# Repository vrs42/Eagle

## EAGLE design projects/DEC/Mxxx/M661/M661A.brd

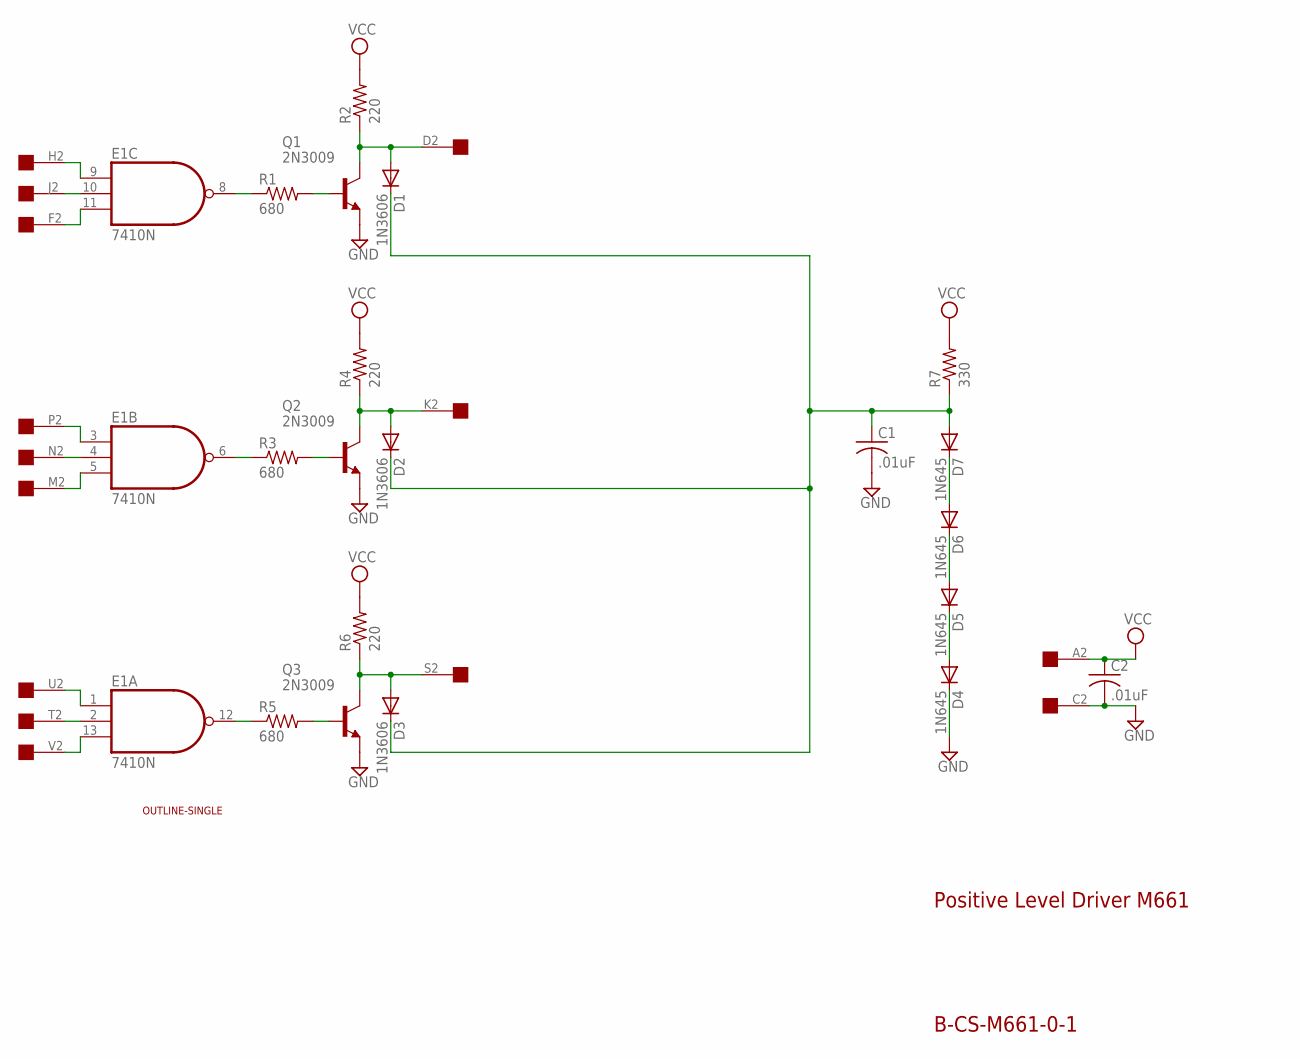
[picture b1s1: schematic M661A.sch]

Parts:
C1, C2: .01uF; C050-025X075
D1, D2, D3: 1N3606; DO35-10
D4, D5, D6, D7: 1N645; DO35-10
E1: 7410N; DIL14
Q1, Q2, Q3: 2N3009; TO5
R1, R3, R5: 680; 0207/10
R2, R4, R6: 220; 0207/10
R7: 330; 0207/10
U$1: OUTLINE-SINGLE; SINGLE
U$3: EDGE-1; EDGE-CON1

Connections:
GND: C1.2, C2.2, D4.C, E1.7 (GND), Q1.1 (E), Q2.1 (E), Q3.1 (E), U$3.C2
unnamed: E1.10 (I1), U$3.J2
unnamed: E1.9 (I0), U$3.H2
unnamed: E1.8 (O), R1.1
unnamed: Q1.2 (B), R1.2
unnamed: E1.4 (I1), U$3.N2
unnamed: D1.A, Q1.3 (C), R2.1, U$3.D2
unnamed: E1.2 (I1), U$3.T2
unnamed: E1.1 (I0), U$3.U2
unnamed: E1.3 (I0), U$3.P2
unnamed: E1.6 (O), R3.1
unnamed: D2.A, Q2.3 (C), R4.1, U$3.K2
unnamed: C1.1, D1.C, D2.C, D3.C, D7.A, R7.1
unnamed: D4.A, D5.C
unnamed: D5.A, D6.C
unnamed: E1.5 (I2), U$3.M2
unnamed: Q2.2 (B), R3.2
unnamed: E1.12 (O), R5.1
unnamed: D3.A, Q3.3 (C), R6.1, U$3.S2
unnamed: D6.A, D7.C
unnamed: E1.11 (I2), U$3.F2
unnamed: E1.13 (I2), U$3.V2
unnamed: Q3.2 (B), R5.2
VCC: C2.1, E1.14 (VCC), R2.2, R4.2, R6.2, R7.2, U$3.A2

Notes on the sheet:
Positive Level Driver M661
B-CS-M661-0-1

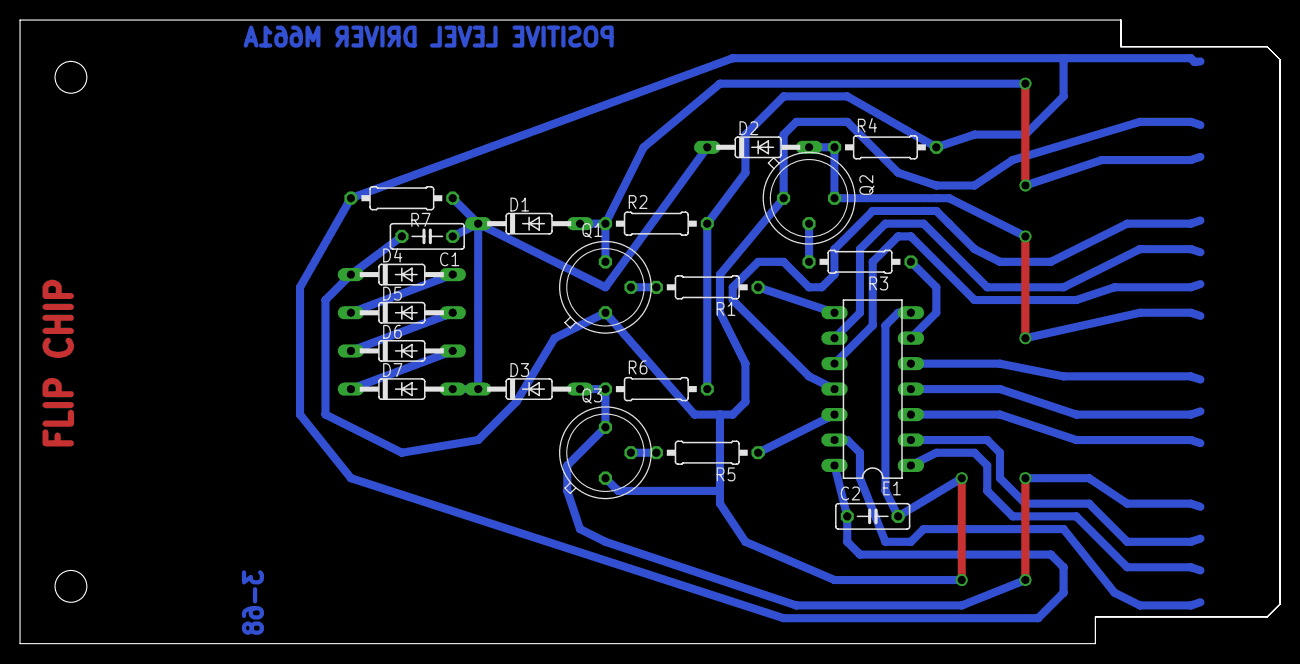
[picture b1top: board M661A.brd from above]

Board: 2 copper layers, 125.7 x 62.2 mm, 23 parts (0 on the bottom side), 24 nets.

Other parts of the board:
U$2: FLIPCHIP

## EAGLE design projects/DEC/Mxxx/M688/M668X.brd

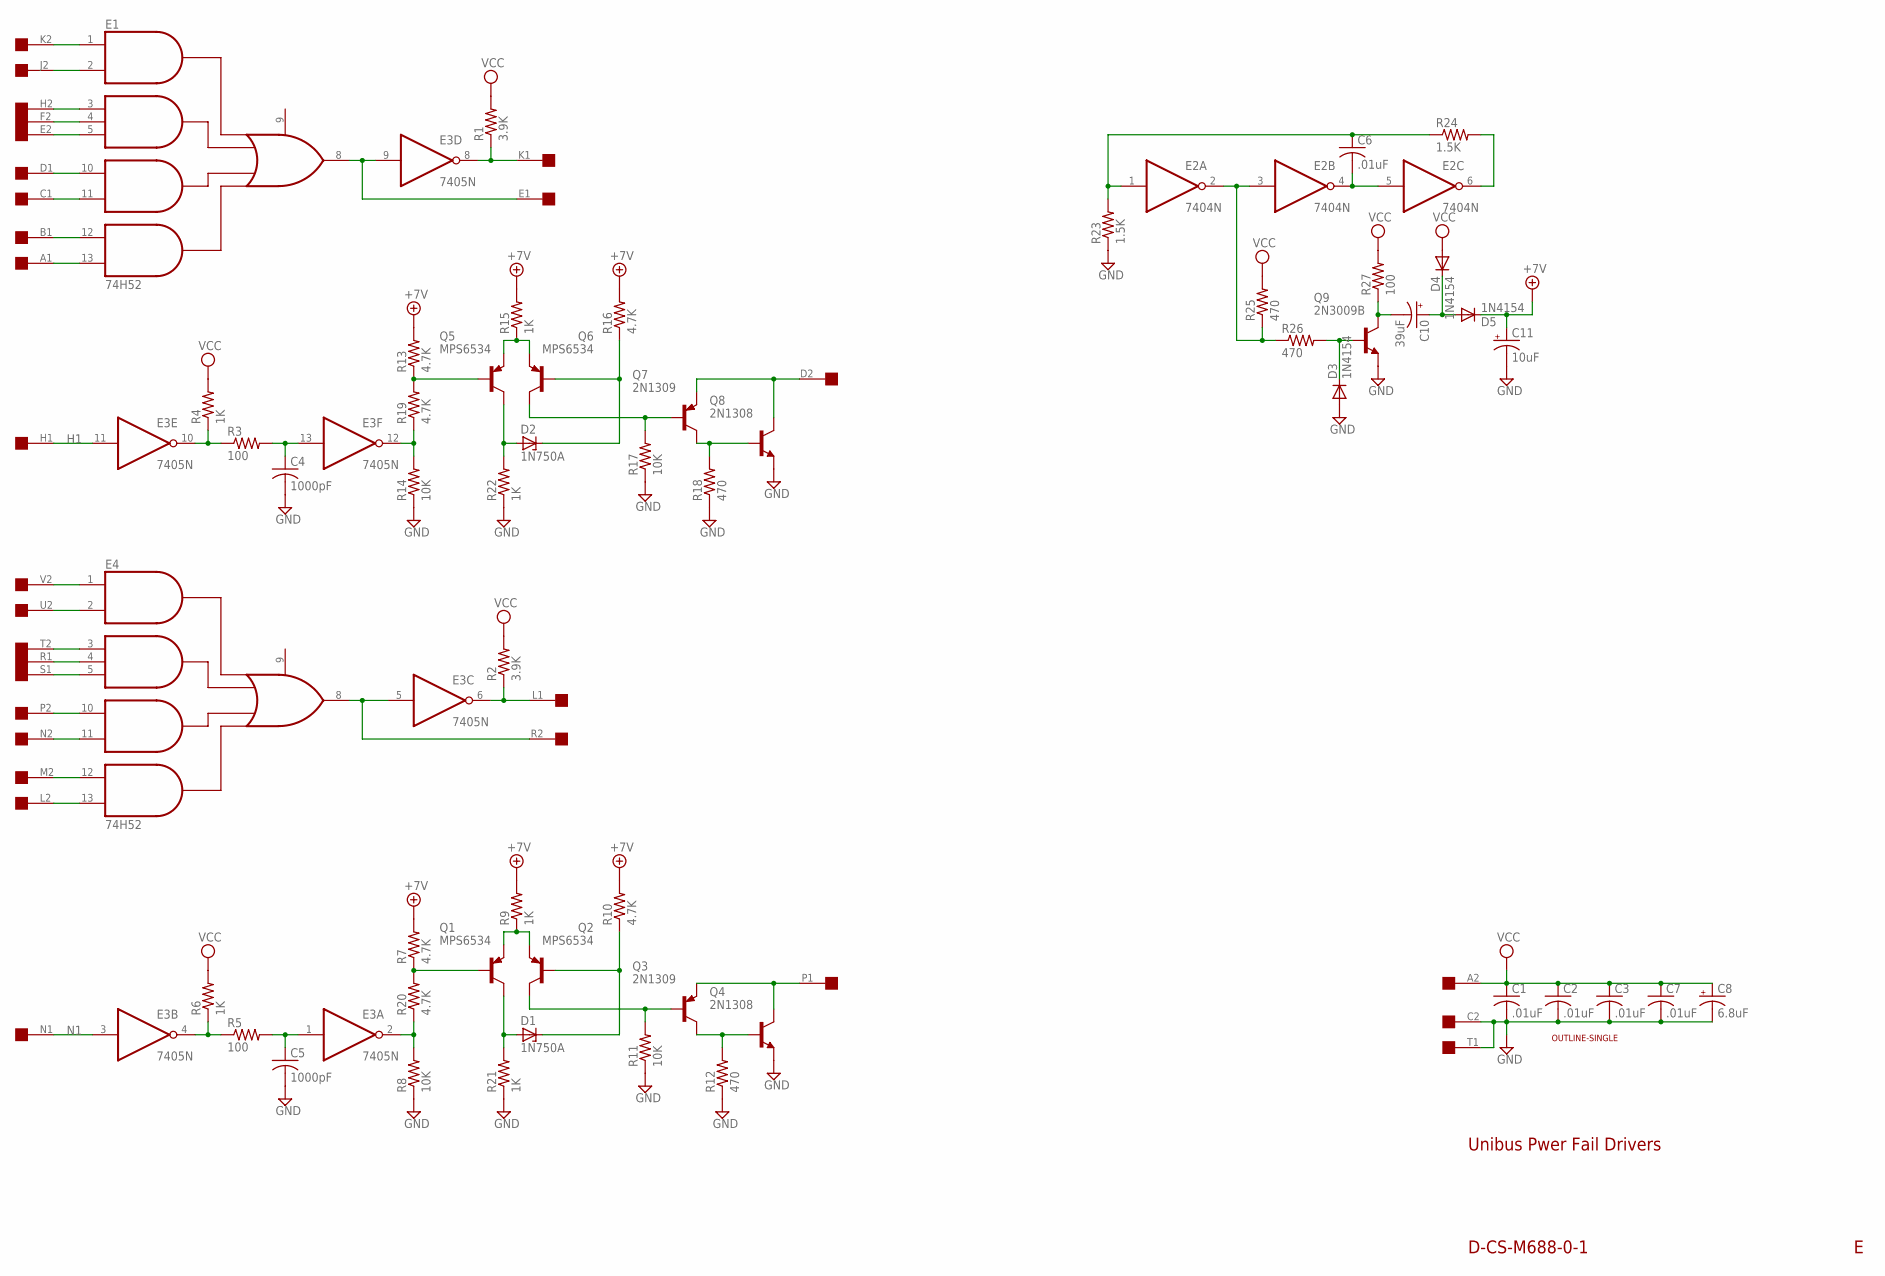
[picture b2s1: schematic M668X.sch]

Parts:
C1, C2, C3, C6, C7: .01uF; C050-025X075
C4, C5: 1000pF; C050-025X075
C8: 6.8uF; E12-8
C10: 39uF; E12-8
C11: 10uF; E12-8
D1, D2: 1N750A; DO35Z10
D3, D4, D5: 1N4154; DO35-10
E1, E4: 74H52; DIL14
E2: 7404N; DIL14
E3: 7405N; DIL14
Q1, Q2, Q5, Q6: MPS6534; TO5
Q3, Q7: 2N1309; TO5
Q4, Q8: 2N1308; TO5
Q9: 2N3009B; TO5
R1, R2: 3.9K; 0207/10
R3, R5, R27: 100; 0207/10
R4, R6, R9, R15, R21, R22: 1K; 0207/10
R7, R10, R13, R16, R19, R20: 4.7K; 0207/10
R8, R11, R14, R17: 10K; 0207/10
R12, R18, R25, R26: 470; 0207/10
R23, R24: 1.5K; 0207/10
U$1: OUTLINE-SINGLE; SINGLE
U$2: SINGLE; EDGE-CON2

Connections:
+7V: C11.+, D5.C, R7.2, R9.2, R10.2, R13.2, R15.2, R16.2
B1: E1.12 (I12), U$2.B1
C1: E1.11 (I11), U$2.C1
D1: E1.10 (I10), U$2.D1
D2: Q7.1 (E), Q8.3 (C), U$2.D2
E1: E1.8 (O8), E3.9 (I), U$2.E1
E2: E1.5 (I5), U$2.E2
F2: E1.4 (I4), U$2.F2
GND: C1.2, C2.2, C3.2, C4.2, C5.2, C7.2, C8.-, C11.-, D3.A, E1.7 (GND), E2.7 (GND), E3.7 (GND), E4.7 (GND), Q4.1 (E), Q8.1 (E), Q9.1 (E), R8.1, R11.1, R12.1, R14.1, R17.1, R18.1, R21.1, R22.1, R23.1, U$2.C2, U$2.T1
H1: E3.11 (I), U$2.H1
H2: E1.3 (I3), U$2.H2
J2: E1.2 (I2), U$2.J2
K1: E3.8 (O), R1.1, U$2.K1
K2: E1.1 (I1), U$2.K2
L1: E3.6 (O), R2.1, U$2.L1
L2: E4.12 (I12), U$2.M2
M2: E4.13 (I13), U$2.L2
N1: E3.3 (I), U$2.N1
N2: E4.11 (I11), U$2.N2
unnamed: E1.13 (I13), U$2.A1
unnamed: E3.10 (O), R3.1, R4.1
unnamed: C4.1, E3.13 (I), R3.2
unnamed: Q5.2 (B), R13.1, R19.2
unnamed: E3.12 (O), R14.2, R19.1
unnamed: Q5.1 (E), Q6.1 (E), R15.1
unnamed: D2.A, Q5.3 (C), R22.2
unnamed: D2.C, Q6.2 (B), R16.1
unnamed: Q6.3 (C), Q7.2 (B), R17.2
unnamed: Q7.3 (C), Q8.2 (B), R18.2
unnamed: E3.4 (O), R5.1, R6.1
unnamed: C5.1, E3.1 (I), R5.2
unnamed: Q1.2 (B), R7.1, R20.2
unnamed: E3.2 (O), R8.2, R20.1
unnamed: Q1.1 (E), Q2.1 (E), R9.1
unnamed: D1.A, Q1.3 (C), R21.2
unnamed: D1.C, Q2.2 (B), R10.1
unnamed: Q2.3 (C), Q3.2 (B), R11.2
unnamed: Q3.3 (C), Q4.2 (B), R12.2
unnamed: E2.2 (O), E2.3 (I), R25.1, R26.1
unnamed: C6.2, E2.4 (O), E2.5 (I)
unnamed: C6.1, E2.1 (I), R23.2, R24.1
unnamed: E2.6 (O), R24.2
unnamed: D3.C, Q9.2 (B), R26.2
unnamed: C10.-, Q9.3 (C), R27.1
unnamed: C10.+, D4.C, D5.A
P1: Q3.1 (E), Q4.3 (C), U$2.P1
P2: E4.10 (I10), U$2.P2
R1: E4.4 (I4), U$2.R1
R2: E3.5 (I), E4.8 (O8), U$2.R2
S1: E4.5 (I5), U$2.S1
T2: E4.3 (I3), U$2.T2
U2: E4.2 (I2), U$2.U2
V2: E4.1 (I1), U$2.V2
VCC: C1.1, C2.1, C3.1, C7.1, C8.+, D4.A, E1.14 (VCC), E2.14 (VCC), E3.14 (VCC), E4.14 (VCC), R1.2, R2.2, R4.2, R6.2, R25.2, R27.2, U$2.A2

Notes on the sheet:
Unibus Pwer Fail Drivers
D-CS-M688-0-1

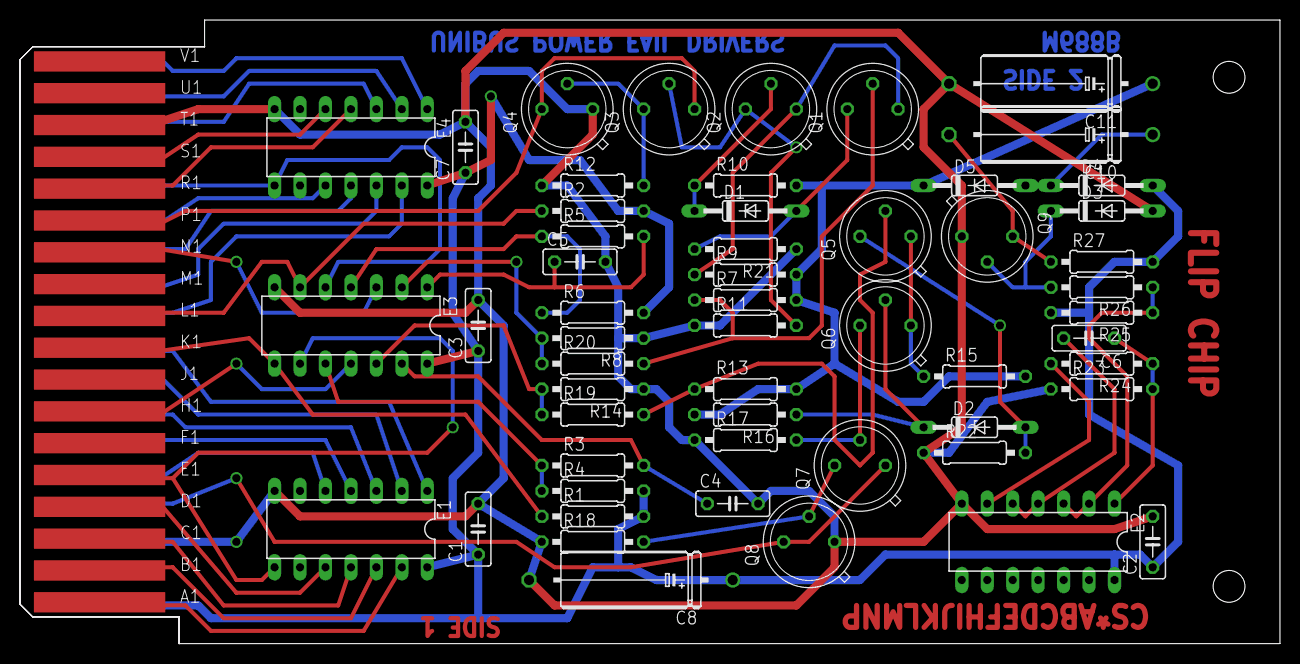
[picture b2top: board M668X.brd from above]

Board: 2 copper layers, 125.7 x 62.2 mm, 57 parts (0 on the bottom side), 54 nets.

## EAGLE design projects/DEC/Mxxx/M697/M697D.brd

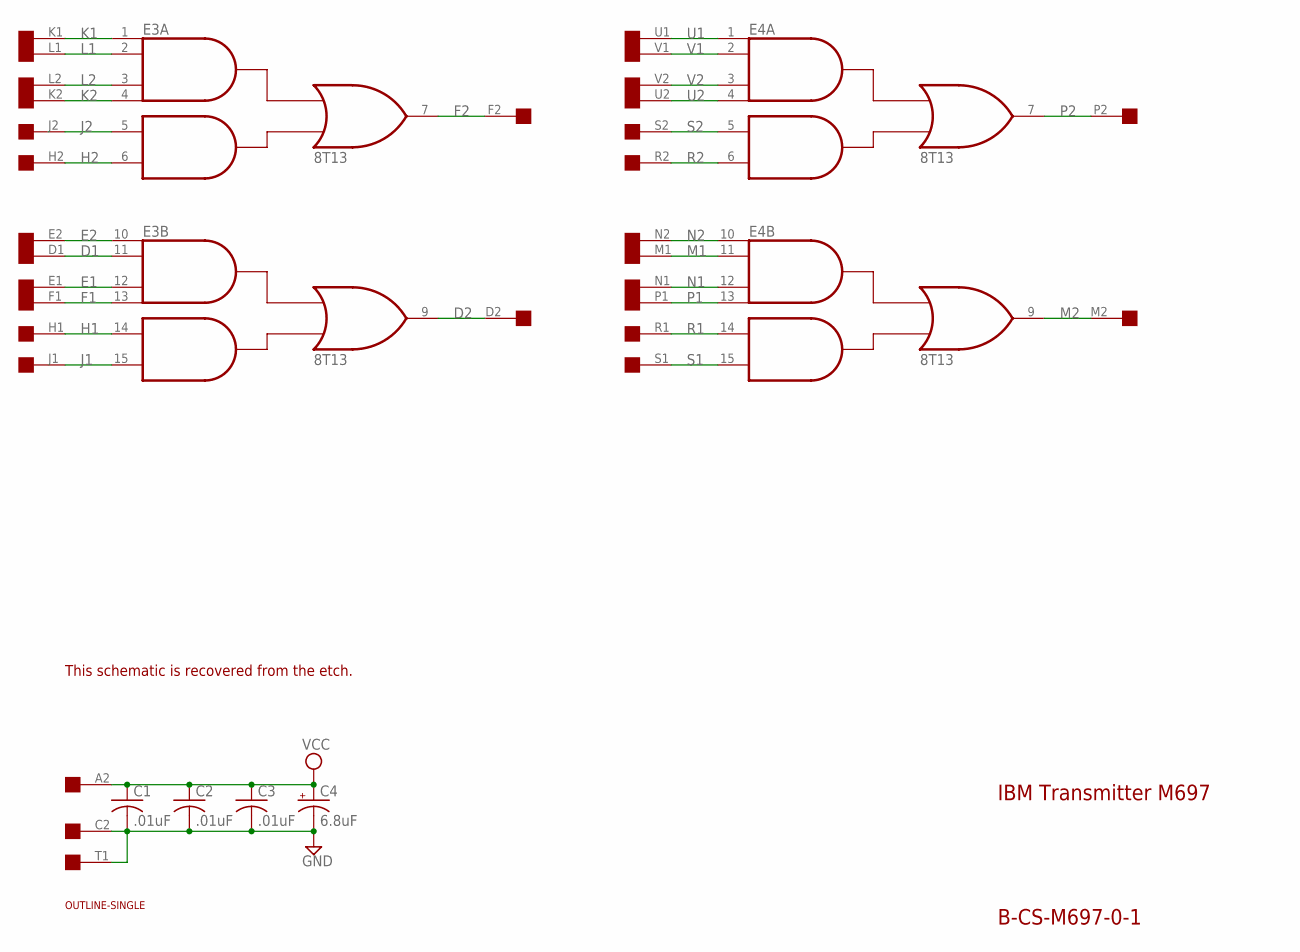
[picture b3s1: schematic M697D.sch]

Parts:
C1, C2, C3: .01uF; C050-025X075
C4: 6.8uF; E12-8
E3, E4: 8T13; DIL16
U$2: SINGLE; EDGE-CON2
U$4: OUTLINE-SINGLE; SINGLE

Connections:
D1: E3.11 (A2), U$2.D1
D2: E3.9 (O), U$2.D2
E1: E3.12 (A3), U$2.E1
E2: E3.10 (A1), U$2.E2
F1: E3.13 (A4), U$2.F1
F2: E3.7 (O), U$2.F2
GND: C1.2, C2.2, C3.2, C4.-, E3.8 (GND), E4.8 (GND), U$2.C2, U$2.T1
H1: E3.14 (B1), U$2.H1
H2: E3.6 (B2), U$2.H2
J1: E3.15 (B2), U$2.J1
J2: E3.5 (B1), U$2.J2
K1: E3.1 (A1), U$2.K1
K2: E3.4 (A4), U$2.K2
L1: E3.2 (A2), U$2.L1
L2: E3.3 (A3), U$2.L2
M1: E4.11 (A2), U$2.M1
M2: E4.9 (O), U$2.M2
N1: E4.12 (A3), U$2.N1
N2: E4.10 (A1), U$2.N2
P1: E4.13 (A4), U$2.P1
P2: E4.7 (O), U$2.P2
R1: E4.14 (B1), U$2.R1
R2: E4.6 (B2), U$2.R2
S1: E4.15 (B2), U$2.S1
S2: E4.5 (B1), U$2.S2
U1: E4.1 (A1), U$2.U1
U2: E4.4 (A4), U$2.U2
V1: E4.2 (A2), U$2.V1
V2: E4.3 (A3), U$2.V2
VCC: C1.1, C2.1, C3.1, C4.+, E3.16 (VCC), E4.16 (VCC), U$2.A2

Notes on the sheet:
IBM Transmitter M697
B-CS-M697-0-1
This schematic is recovered from the etch.

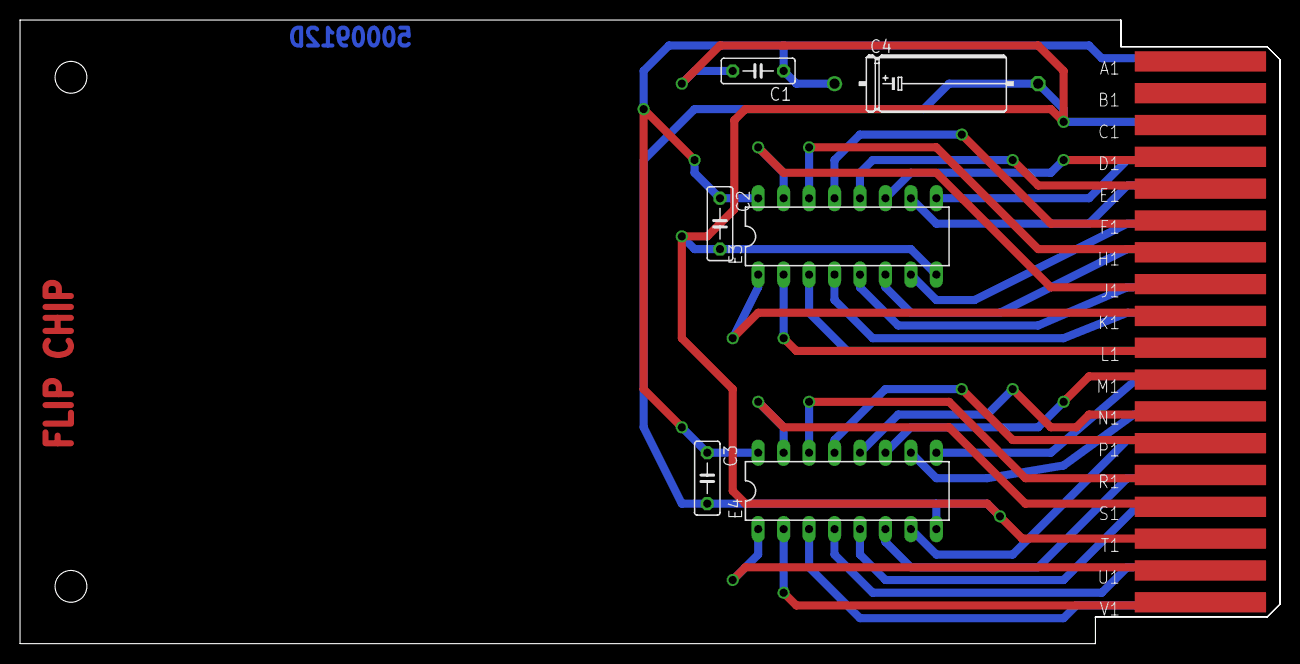
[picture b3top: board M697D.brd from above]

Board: 2 copper layers, 125.7 x 62.2 mm, 9 parts (0 on the bottom side), 30 nets.

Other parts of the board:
U$1: FLIPCHIP

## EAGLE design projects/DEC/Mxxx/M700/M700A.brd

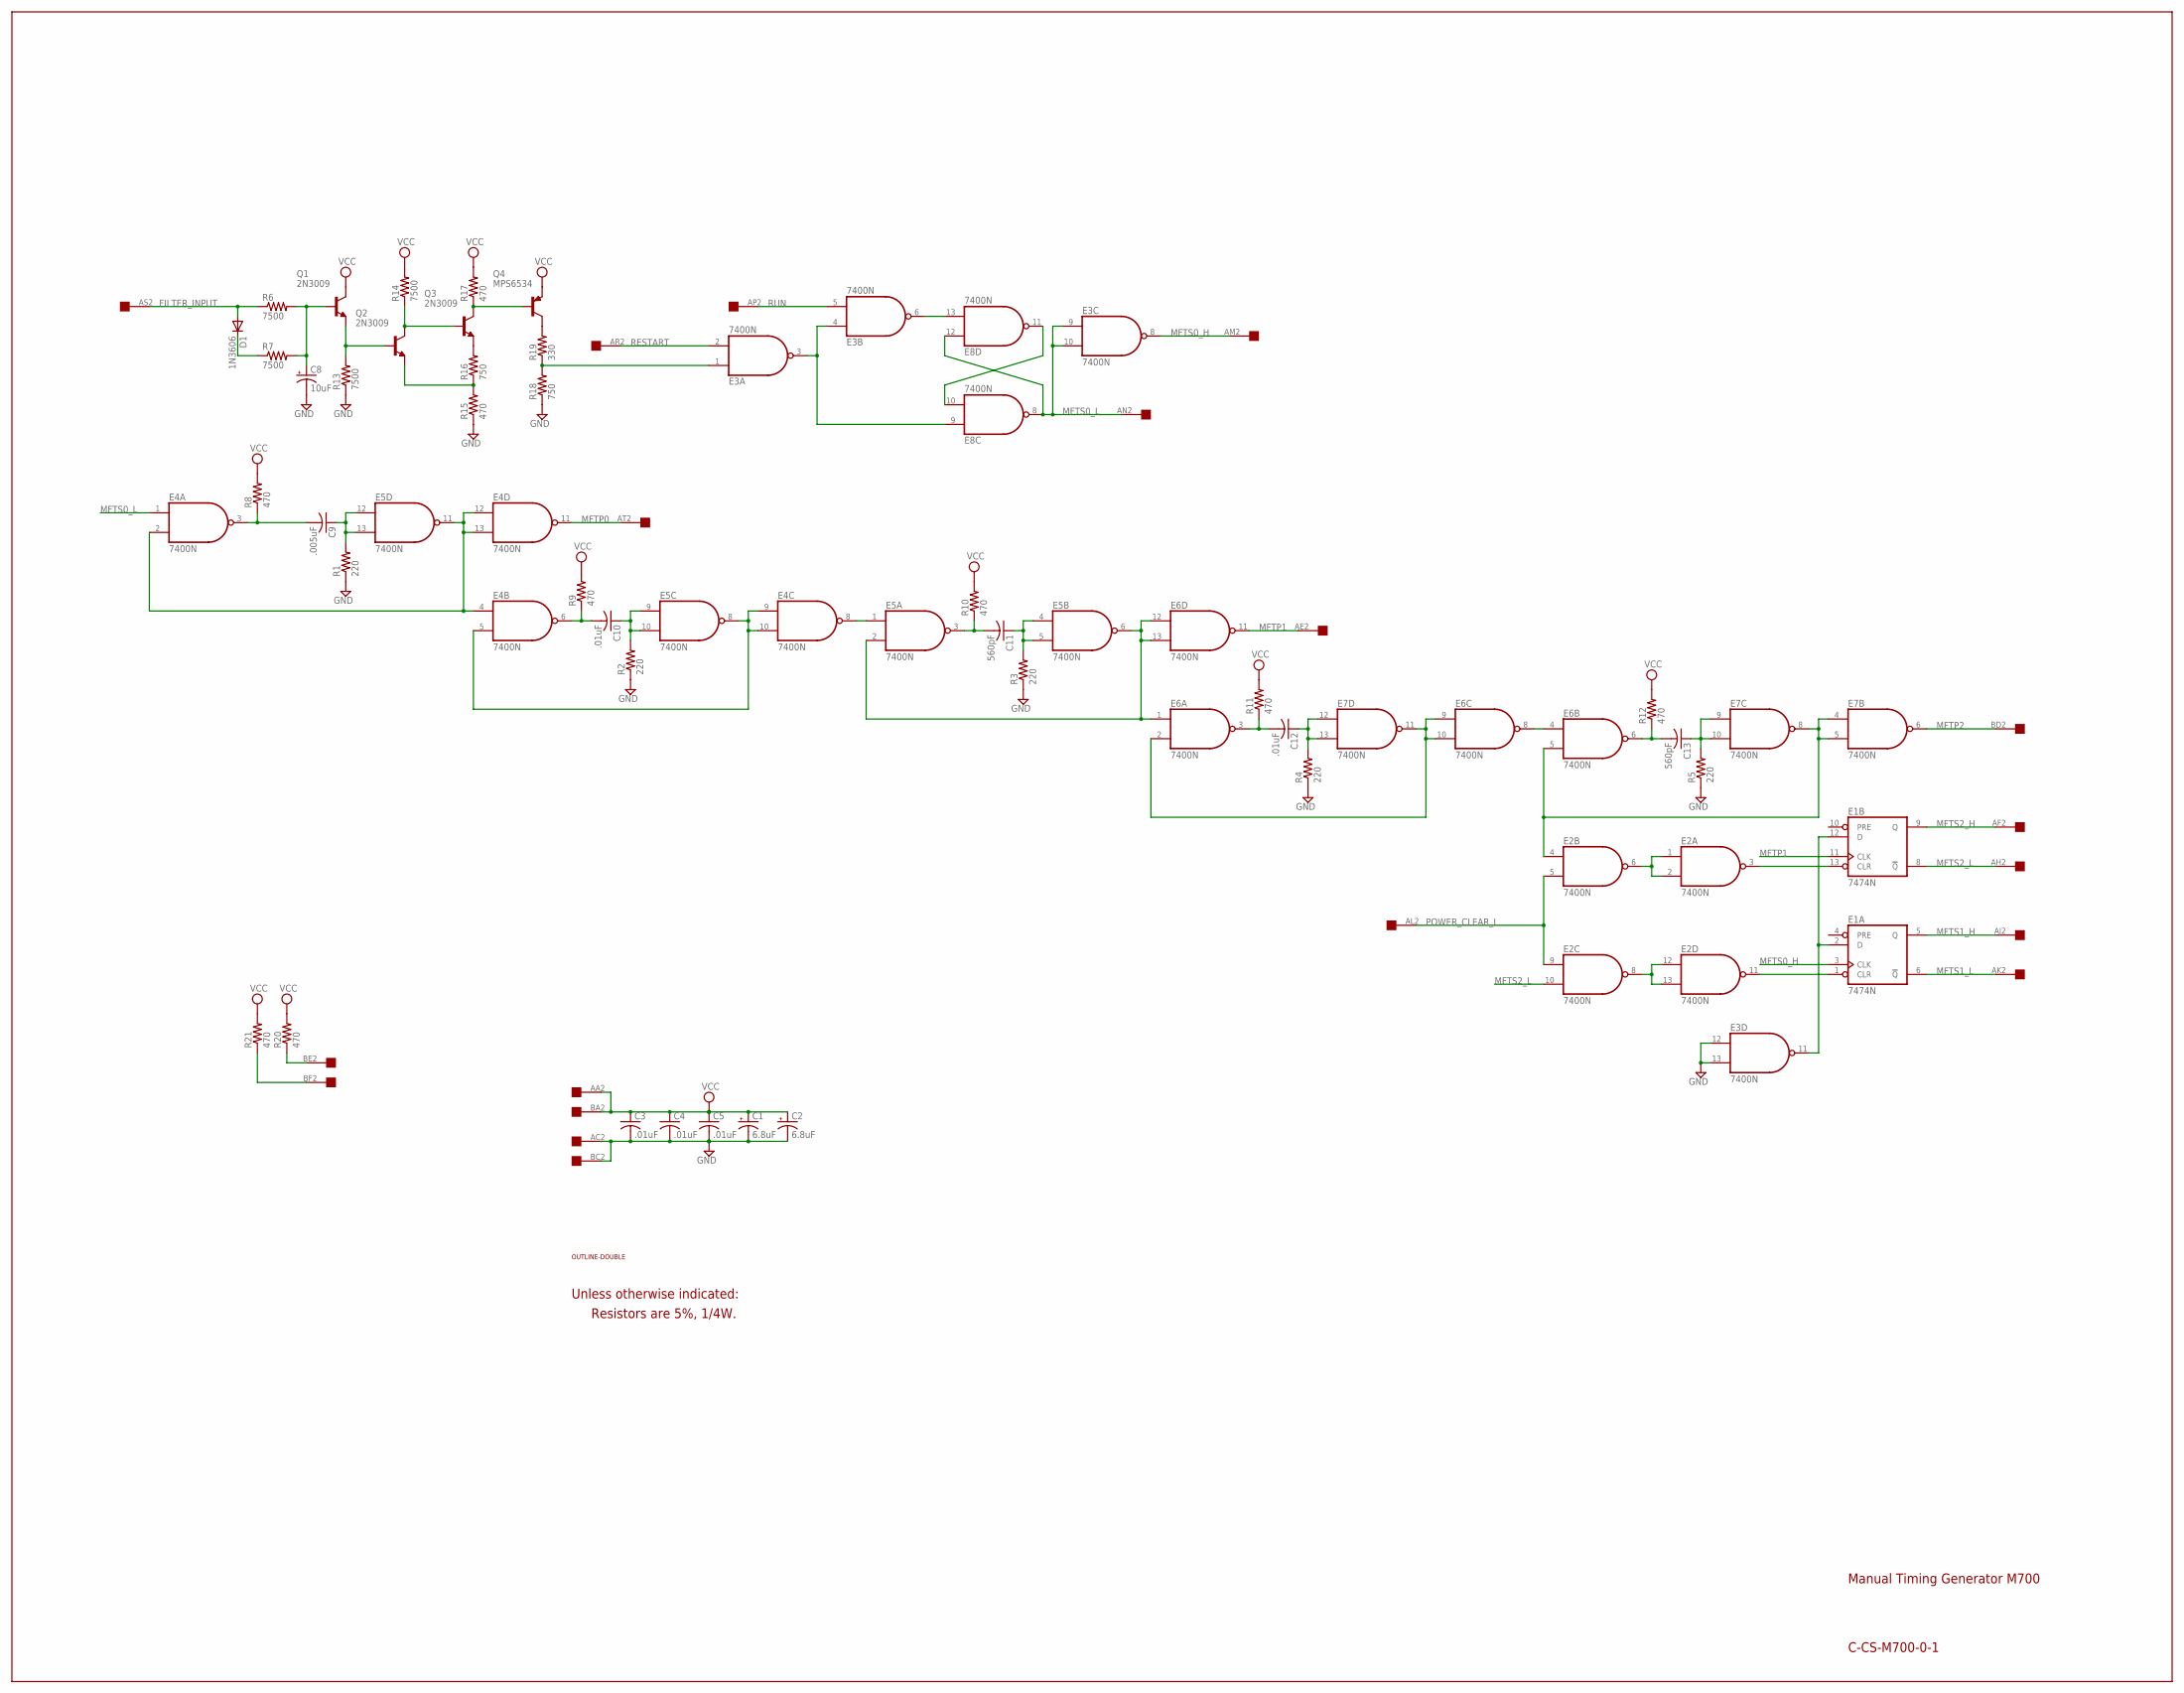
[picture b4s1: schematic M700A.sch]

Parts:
C1, C2: 6.8uF; E15-5
C3, C4, C5, C10, C12: .01uF; C050-025X075
C8: 10uF; E15-5
C9: .005uF; C050-025X075
C11, C13: 560pF; C050-025X075
D1: 1N3606; DO35-10
E1: 7474N; DIL14
E2, E3, E4, E5, E6, E7, E8: 7400N; DIL14
Q1, Q2, Q3: 2N3009; TO5
Q4: MPS6534; TO5
R1, R2, R3, R4, R5: 220; 0207/10
R6, R7, R13, R14: 7500; 0207/10
R8, R9, R10, R11, R12, R15, R17, R20, R21: 470; 0207/10
R16, R18: 750; 0207/10
R19: 330; 0207/10
U$1: DOUBLE; EDGE-CON4
U$2: OUTLINE-DOUBLE; DOUBLE

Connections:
FILTER_INPUT: D1.A, R6.1, U$1.AS2
GND: C1.-, C2.-, C3.2, C4.2, C5.2, C8.-, E1.7 (GND), E2.7 (GND), E3.7 (GND), E3.12 (I0), E3.13 (I1), E4.7 (GND), E5.7 (GND), E6.7 (GND), E7.7 (GND), E8.7 (GND), R1.1, R2.1, R3.1, R4.1, R5.1, R13.1, R15.1, R18.1, U$1.AC2, U$1.BC2
MFTP0: E4.11 (O), U$1.AT2
MFTP1: E1.11 (CLK), E6.11 (O), U$1.AE2
MFTP2: E7.6 (O), U$1.BD2
MFTS0_H: E1.3 (CLK), E3.8 (O), U$1.AM2
MFTS0_L: E3.9 (I0), E3.10 (I1), E4.1 (I0), E8.8 (O), E8.12 (I0), U$1.AN2
MFTS1_H: E1.5 (Q), U$1.AJ2
MFTS1_L: E1.6 (!Q), U$1.AK2
MFTS2_H: E1.9 (Q), U$1.AF2
MFTS2_L: E1.8 (!Q), E2.10 (I1), U$1.AH2
unnamed: E1.13 (CLR), E2.3 (O)
unnamed: E2.4 (I0), E6.5 (I1), E7.4 (I0), E7.5 (I1), E7.8 (O)
unnamed: C13.1, E7.9 (I0), E7.10 (I1), R5.2
unnamed: C13.2, E6.6 (O), R12.1
unnamed: E2.1 (I0), E2.2 (I1), E2.6 (O)
unnamed: C8.+, Q1.2 (B), R6.2, R7.2
unnamed: E1.2 (D), E1.12 (D), E3.11 (O)
unnamed: D1.C, R7.1
unnamed: Q2.3 (C), Q3.2 (B), R14.1
unnamed: Q1.1 (E), Q2.2 (B), R13.2
unnamed: R21.1, U$1.BF2
unnamed: R20.1, U$1.BE2
unnamed: Q3.3 (C), Q4.2 (B), R17.1
unnamed: Q3.1 (E), R16.2
unnamed: Q2.1 (E), R15.2, R16.1
unnamed: Q4.3 (C), R19.2
unnamed: E3.1 (I0), R18.2, R19.1
unnamed: E3.3 (O), E3.4 (I0), E8.9 (I0)
unnamed: E8.10 (I1), E8.11 (O)
unnamed: C9.1, E5.12 (I0), E5.13 (I1), R1.2
unnamed: E3.6 (O), E8.13 (I1)
unnamed: C9.2, E4.3 (O), R8.1
unnamed: E4.2 (I1), E4.4 (I0), E4.12 (I0), E4.13 (I1), E5.11 (O)
unnamed: C10.2, E4.6 (O), R9.1
unnamed: C10.1, E5.9 (I0), E5.10 (I1), R2.2
unnamed: E4.5 (I1), E4.9 (I0), E4.10 (I1), E5.8 (O)
unnamed: C11.2, E5.3 (O), R10.1
unnamed: E4.8 (O), E5.1 (I0)
unnamed: C11.1, E5.4 (I0), E5.5 (I1), R3.2
unnamed: E5.2 (I1), E5.6 (O), E6.1 (I0), E6.12 (I0), E6.13 (I1)
unnamed: C12.2, E6.3 (O), R11.1
unnamed: C12.1, E7.12 (I0), E7.13 (I1), R4.2
unnamed: E6.2 (I1), E6.9 (I0), E6.10 (I1), E7.11 (O)
unnamed: E2.8 (O), E2.12 (I0), E2.13 (I1)
unnamed: E6.4 (I0), E6.8 (O)
unnamed: E1.1 (CLR), E2.11 (O)
POWER_CLEAR_L: E2.5 (I1), E2.9 (I0), U$1.AL2
RESTART: E3.2 (I1), U$1.AR2
RUN: E3.5 (I1), U$1.AP2
VCC: C1.+, C2.+, C3.1, C4.1, C5.1, E1.14 (VCC), E2.14 (VCC), E3.14 (VCC), E4.14 (VCC), E5.14 (VCC), E6.14 (VCC), E7.14 (VCC), E8.14 (VCC), Q1.3 (C), Q4.1 (E), R8.2, R9.2, R10.2, R11.2, R12.2, R14.2, R17.2, R20.2, R21.2, U$1.AA2, U$1.BA2

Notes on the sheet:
Manual Timing Generator M700
C-CS-M700-0-1
Unless otherwise indicated:
Resistors are 5%, 1/4W.

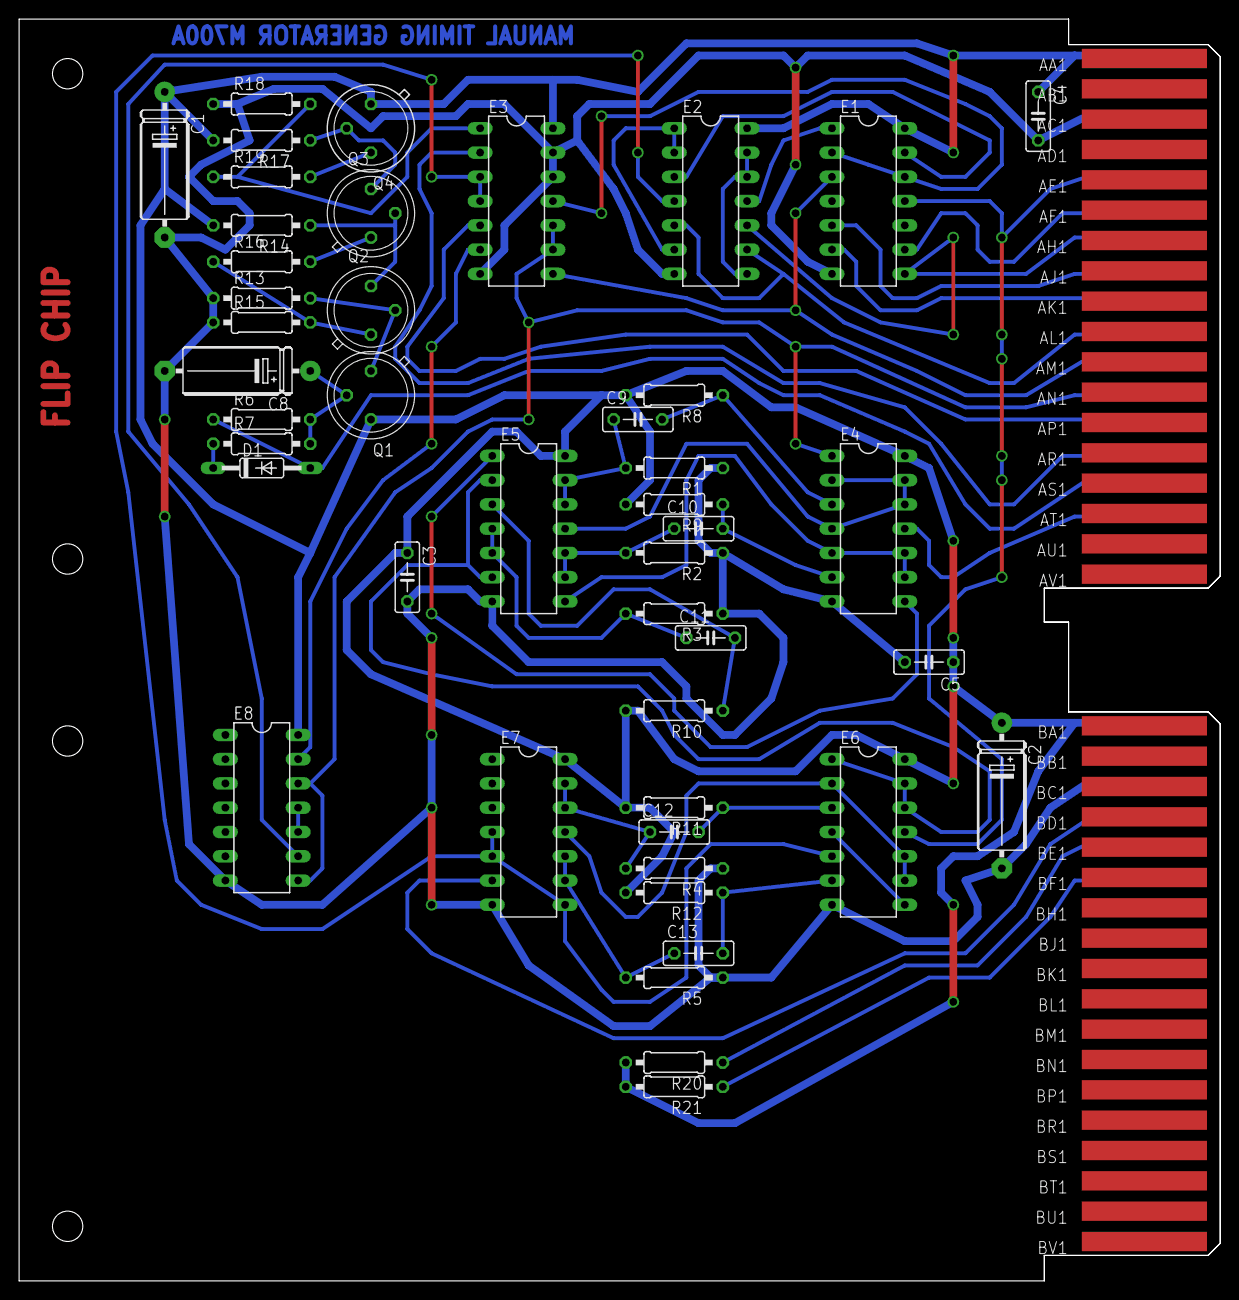
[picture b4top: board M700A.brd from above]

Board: 2 copper layers, 125.7 x 132.1 mm, 48 parts (0 on the bottom side), 51 nets.

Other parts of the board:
U$4: FLIPCHIP
